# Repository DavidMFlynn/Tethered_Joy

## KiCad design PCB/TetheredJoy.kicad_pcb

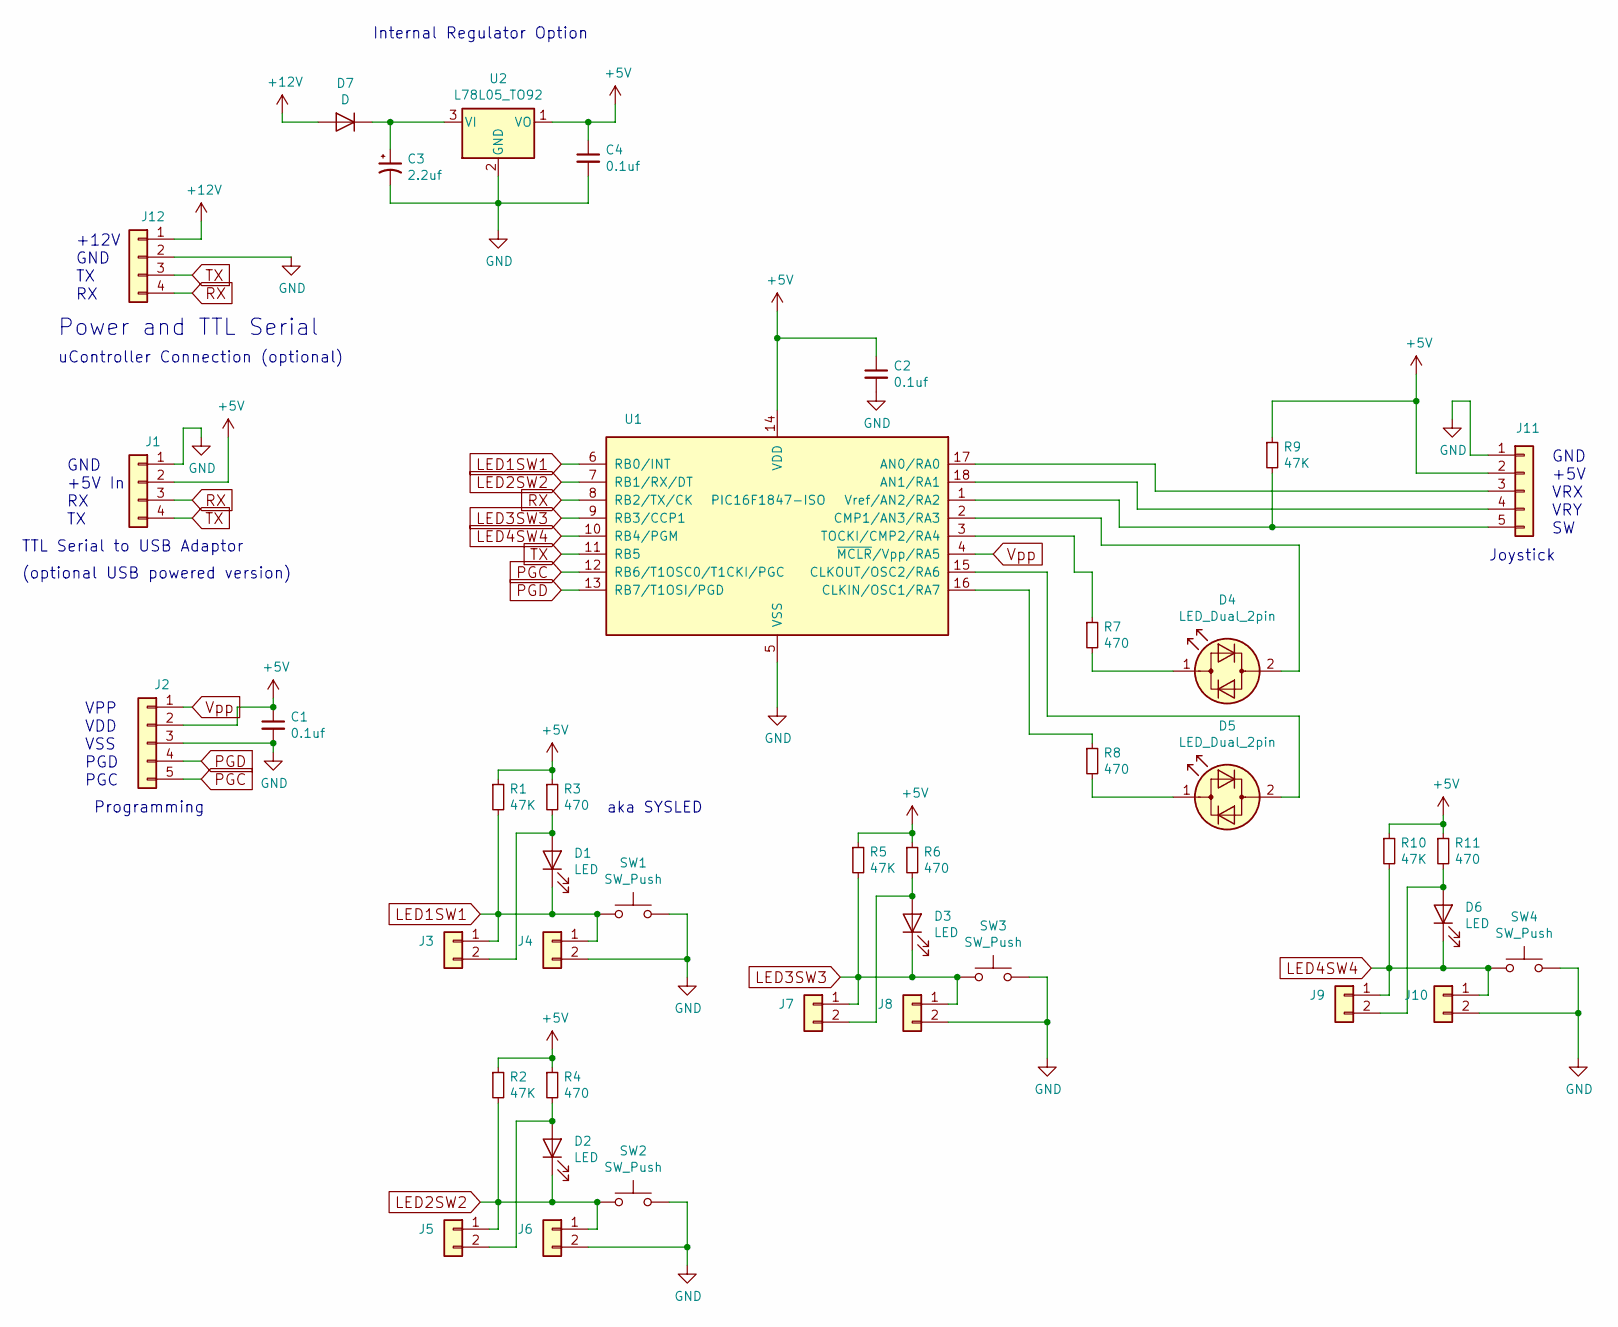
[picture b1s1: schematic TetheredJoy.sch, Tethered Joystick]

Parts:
C1, C2, C4: 0.1uf; C_0805_2012Metric_Pad1.15x1.40mm_HandSolder
C3: 2.2uf; CP_Radial_D4.0mm_P2.00mm
D1, D2, D3, D6: LED; LED_1206_3216Metric_Pad1.42x1.75mm_HandSolder
D4, D5: LED_Dual_2pin; LED_1206_3216Metric_Pad1.42x1.75mm_HandSolder
D7: D; D_SMA_Handsoldering
J1, J12: Conn_01x04; PinHeader_1x04_P2.54mm_Vertical
J2, J11: Conn_01x05; PinHeader_1x05_P2.54mm_Vertical
J3, J4, J5, J6, J7, J8, J9, J10: Conn_01x02; PinHeader_1x02_P2.54mm_Vertical
R1, R2, R5, R9, R10: 47K; R_0805_2012Metric_Pad1.15x1.40mm_HandSolder
R3, R4, R6, R7, R8, R11: 470; R_0805_2012Metric_Pad1.15x1.40mm_HandSolder
SW1, SW2, SW3, SW4: SW_Push; SW_SPST_PTS645
U1: PIC16F1847-ISO; SOIC-18W_7.5x11.6mm_P1.27mm
U2: L78L05_TO92; TO-92_Inline

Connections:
+5V: C1.1, C2.1, C4.1, J1.2, J2.2, J11.2, R1.1, R2.1, R3.1, R4.1, R5.1, R6.1, R9.1, R10.1, R11.1, U1.14 (VDD), U2.1 (VO)
+12V: D7.2 (A), J12.1
GND: C1.2, C2.2, C3.2, C4.2, J1.1, J2.3, J4.2, J6.2, J8.2, J10.2, J11.1, J12.2, SW1.2, SW2.2, SW3.2, SW4.2, U1.5 (VSS), U2.2 (GND)
LED1SW1: D1.1 (K), J3.1, J4.1, R1.2, SW1.1, U1.6 (RB0/INT)
LED2SW2: D2.1 (K), J5.1, J6.1, R2.2, SW2.1, U1.7 (RB1/RX/DT)
LED3SW3: D3.1 (K), J7.1, J8.1, R5.2, SW3.1, U1.9 (RB3/CCP1)
LED4SW4: D6.1 (K), J9.1, J10.1, R10.2, SW4.1, U1.10 (RB4/PGM)
unnamed: C3.1, D7.1 (K), U2.3 (VI)
unnamed: D1.2 (A), J3.2, R3.2
unnamed: D2.2 (A), J5.2, R4.2
unnamed: D3.2 (A), J7.2, R6.2
unnamed: D4.1 (KA), R7.2
unnamed: D4.2 (AK), U1.2 (CMP1/AN3/RA3)
unnamed: D5.1 (KA), R8.2
unnamed: D5.2 (AK), U1.15 (CLKOUT/OSC2/RA6)
unnamed: D6.2 (A), J9.2, R11.2
unnamed: J11.3, U1.17 (AN0/RA0)
unnamed: J11.4, U1.18 (AN1/RA1)
unnamed: J11.5, R9.2, U1.1 (Vref/AN2/RA2)
unnamed: R7.1, U1.3 (TOCKI/CMP2/RA4)
unnamed: R8.1, U1.16 (CLKIN/OSC1/RA7)
PGC: J2.5, U1.12 (RB6/T1OSC0/T1CKI/PGC)
PGD: J2.4, U1.13 (RB7/T1OSI/PGD)
RX: J1.3, J12.4, U1.8 (RB2/TX/CK)
TX: J1.4, J12.3, U1.11 (RB5)
Vpp: J2.1, U1.4 (~MCLR~/Vpp/RA5)

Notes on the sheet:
GND +5V In RX TX
VPP VDD VSS PGD PGC
TTL Serial to USB Adaptor
Programming
Joystick
GND +5V VRX VRY SW
aka SYSLED
+12V GND TX RX
Power and TTL Serial
uController Connection (optional)
(optional USB powered version)
Internal Regulator Option

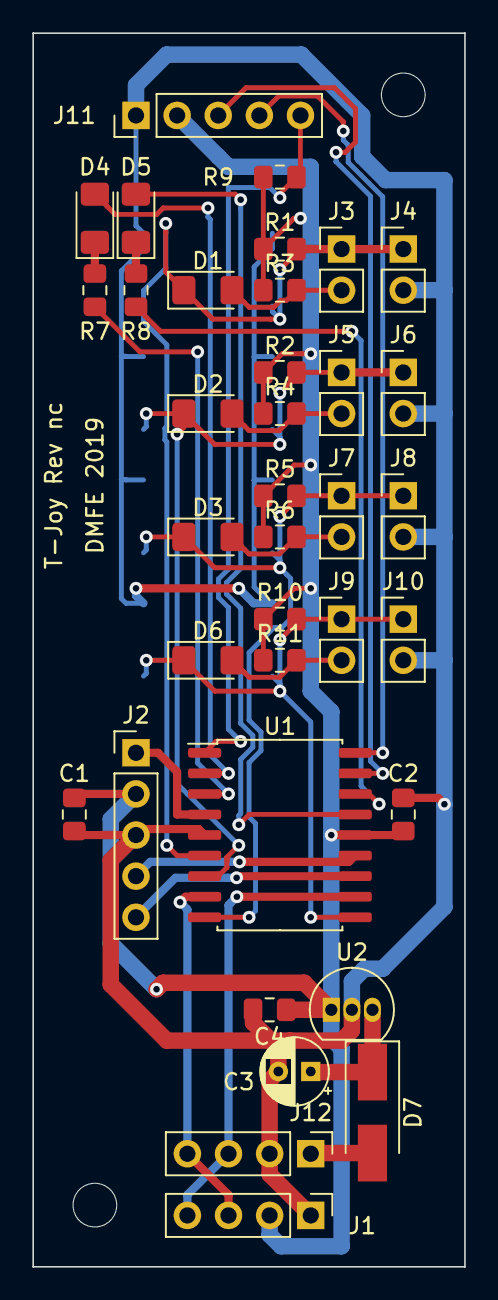
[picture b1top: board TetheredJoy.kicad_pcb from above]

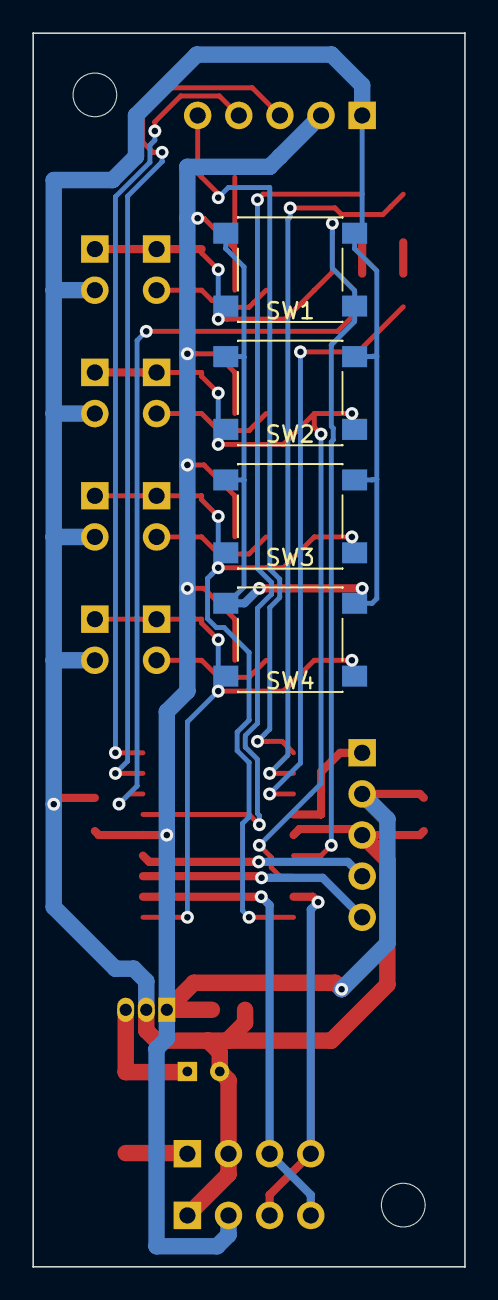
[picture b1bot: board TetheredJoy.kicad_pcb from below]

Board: 2 copper layers, 26.7 x 76.2 mm, 42 parts (4 on the bottom side), 26 nets.

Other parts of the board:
H1, H2: MountingHole_2.7mm_M2.5

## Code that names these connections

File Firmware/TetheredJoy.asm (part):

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;   Mode 4: Gripper force control.
;====================================================================================================
;
;   Pin 1 (RA2/AN2) Joy SW (Active Low Input)
;   Pin 2 (RA3/AN3) D4 Bi-Color LED Red+/Green-
;   Pin 3 (RA4/AN4) D4 Bi-Color LED Red-/Green+
;   Pin 4 (RA5/MCLR*) VPP/MCLR*
;   Pin 5 (GND) Ground
;   Pin 6 (RB0) LED1/SW1 (Active Low Input/Output)(System LED)
;   Pin 7 (RB1/AN11/SDA1) LED2/SW2 (Active Low Input/Output)
;   Pin 8 (RB2/AN10/TX) TTL Serial RX
;   Pin 9 (RB3/CCP1) LED3/SW3 (Active Low Input/Output)
;
;   Pin 10 (RB4/AN8/SLC1) LED4/SW4 (Active Low Input/Output)
;   Pin 11 (RB5/AN7) TTL Serial TX
;   Pin 12 (RB6/AN5/CCP2) ICSPCLK
;   Pin 13 (RB7/AN6) ICSPDAT
;   Pin 14 (Vcc) +5 volts
;   Pin 15 (RA6) D5 Bi-Color LED Red+/Green-
;   Pin 16 (RA7/CCP2) D5 Bi-Color LED Red-/Green+
;   Pin 17 (RA0/AN0) Joy X analog input
;   Pin 18 (RA1/AN1) Joy Y analog input
;
;====================================================================================================
;
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; INTOSC oscillator: I/O function on CLKIN pin
; WDT disabled
; PWRT disabled
; MCLR/VPP pin function is digital input
; Program memory code protection is disabled
; Data memory code protection is disabled
; Brown-out Reset enabled
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#Define	SWJoy_In	PORTA,2	;Joy SW
#Define	BiLED4_RedAnode	PORTA,3	;D4 Bi-Color LED Red+/Green-
#Define	BiLED4_RedCathode	PORTA,4	;D4 Bi-Color LED Red-/Green+
#Define	RA5_In	PORTA,5	;VPP/MCLR*
#Define	BiLED5_RedAnode	PORTA,6	;D5 Bi-Color LED Red+/Green-
#Define	BiLED5_RedCathode	PORTA,7	;D5 Bi-Color LED Red-/Green+
LED4_RBit	EQU	3	;LED4 (High=Red/Low=Green Output)
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
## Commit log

2019-04-07 Starting the PCB
2019-04-10 started code
2019-04-25 worked on schematic
2019-04-26 Schematic done
2019-04-27 Firmware d1 ready to test
2019-04-28 LEDs
2019-04-29 Left grip
2019-06-08 PCB done
2019-06-10 Leds working
2019-06-11 Docs
2019-08-05 schematic pdf
2019-08-11 updates sch.pdf
2019-08-31 default address
